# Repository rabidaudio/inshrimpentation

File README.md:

Shrimp tank monitoring

1. Hardware interface for measuring data
2. Web server for viewing data and configuring
3. sqlite db for storing data

https://pkg.go.dev/github.com/blackjack/webcam
https://periph.io/project/design/
Live stream is handled out-of-band using mediamtx
https://mediamtx.org/docs/read/web-browsers#embed-in-a-website

Because of mediamtx's non-standard build process, it can't be installed with `go install`,
and therefore can't be added directly to gokrazy. Instead, we have a git submodule that
we compile locally, and add to gokrazy using the local directory. This also allows easy
forks and version updates.

Additionally, it's rPi camera interface isn't statically compiled and thus cannot run on gokrazy.
Instead, we manually load ffmpeg onto the image and use that for accessing the camera.

TODO: could we compile our own simple v4l2 -> rtsp program in go??
Could run ffmpeg in docker via podman
Could try compiling mtxrpi in the gokrazy docker image
Could load rpicam-vid manually

https://github.com/AlexxIT/go2rtc

db:
    sqlite db for storing measurements, configs
instruments/*:
    interface for measuring
scheduler:
    at certain times, queries instruments, saves to db. if outside levels, send alert
server:
    api for accessing data
frontend:
    svelte spi for displaying data

WaterLevel
    measurements: inches
    alarms:
        less than 7.5 inches
        greater than 8.5 inches
Temperature
    measurements: celcius
    alarms:
        less than 20 C (68F)
        more than 23 C (73.5F)
Brightness:
    measurements: (arbitrary - relative measure, range TBD)

https://cad.onshape.com/documents/8f74ccdbefb985152d23f960/w/87353d4eeef811a2b8056367/e/cb90858fdb4eb002a92e8198

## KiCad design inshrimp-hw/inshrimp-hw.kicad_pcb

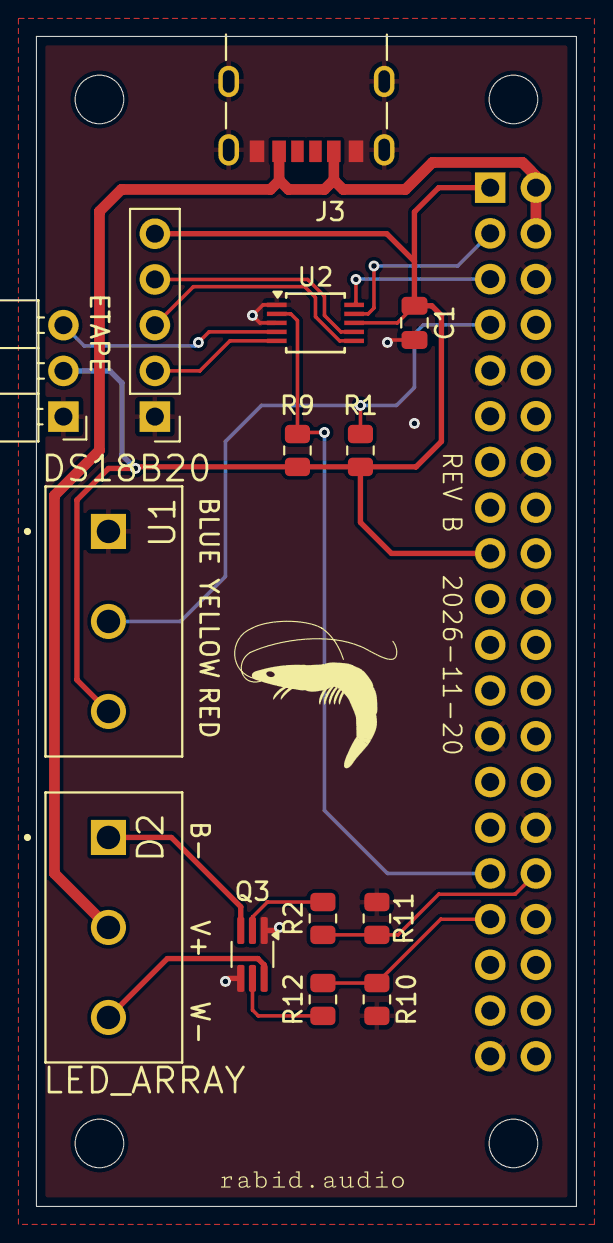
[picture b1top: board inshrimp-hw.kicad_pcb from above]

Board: 2 copper layers, 30.0 x 65.0 mm, 19 parts (1 on the bottom side), 17 nets.

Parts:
C1: 100n; C_0805_2012Metric
D2: LED_ARRAY; CUI_TB002-500-03BE
H1, H2, H3, H4: MountingHole; MountingHole_2.7mm_M2.5
J1: Raspberry_Pi_Zero_2W; PinSocket_2x20_P2.54mm_Vertical
J2: ADC_CONN; PinHeader_1x05_P2.54mm_Vertical
J3: USB_C_Receptacle_PowerOnly_6P; AMPHENOL_10164359-00011LF
Q3: Q_Dual_NMOS; SOT-363_SC-70-6_Handsoldering
R1, R9, R10, R11: 4.7k; R_0805_2012Metric
R2, R12: 47; R_0805_2012Metric
U1: DS18B20; CUI_TB002-500-03BE
U2: ADS1015IDGS; TSSOP-10_3x3mm_P0.5mm
U3: ETAPE; PinHeader_1x03_P2.54mm_Horizontal

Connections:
+3.3V: C1.1, J1.1 (3V3), J1.17 (3V3), J2.5, R1.1, R9.1, U1.3 (V_{DD}), U2.8 (VDD), U3.2 (VCC)
+5V: D2.2 (V+), J1.2 (5V), J1.4 (5V), J3.A9 (VBUS), J3.B9 (VBUS)
ADC_READY: J1.31 (GPCLK2/GPIO06), R9.2, U2.2 (ALERT/RDY)
BRIGHTNESS: J2.2, U2.5 (AIN1)
FUTURE: J2.4, U2.7 (AIN3)
GND: C1.2, J1.6 (GND), J1.9 (GND), J1.14 (GND), J1.20 (GND), J1.25 (GND), J1.30 (GND), J1.34 (GND), J1.39 (GND), J2.1, J3.A12 (GND), J3.B12 (GND), J3.S1 (SHIELD), Q3.1 (S), Q3.4 (S), R10.2, R11.2, U1.1 (GND), U2.1 (ADDR), U2.3 (GND), U3.1 (GND)
LEDS_B: J1.33 (GPIO13/PWM1), R10.1, R12.2
LEDS_W: J1.32 (GPIO12/PWM0), R2.1, R11.1
unnamed: D2.1 (B-), Q3.3 (D)
unnamed: D2.3 (W-), Q3.6 (D)
unnamed: Q3.2 (G), R2.2
unnamed: Q3.5 (G), R12.1
ONEWIRE: J1.7 (GPCLK0/GPIO04), R1.2, U1.2 (DQ)
REDNESS: J2.3, U2.6 (AIN2)
SCL: J1.5 (SCL_I2C1/GPIO03), U2.10 (SCL)
SDA: J1.3 (SDA_I2C1/GPIO02), U2.9 (SDA)
WATER_LEVEL: U2.4 (AIN0), U3.3 (VREF)
